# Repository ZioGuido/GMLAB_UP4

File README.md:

# GMLAB_UP4
Open-source Programmable USB Expression Pedal

This is the repository for the GMLAB UP4 pedal.

See the product at: www.GmLab.it

Buy it at www.MyRigShop.com

Visit www.GenuineSoundware.com - www.Crumar.it

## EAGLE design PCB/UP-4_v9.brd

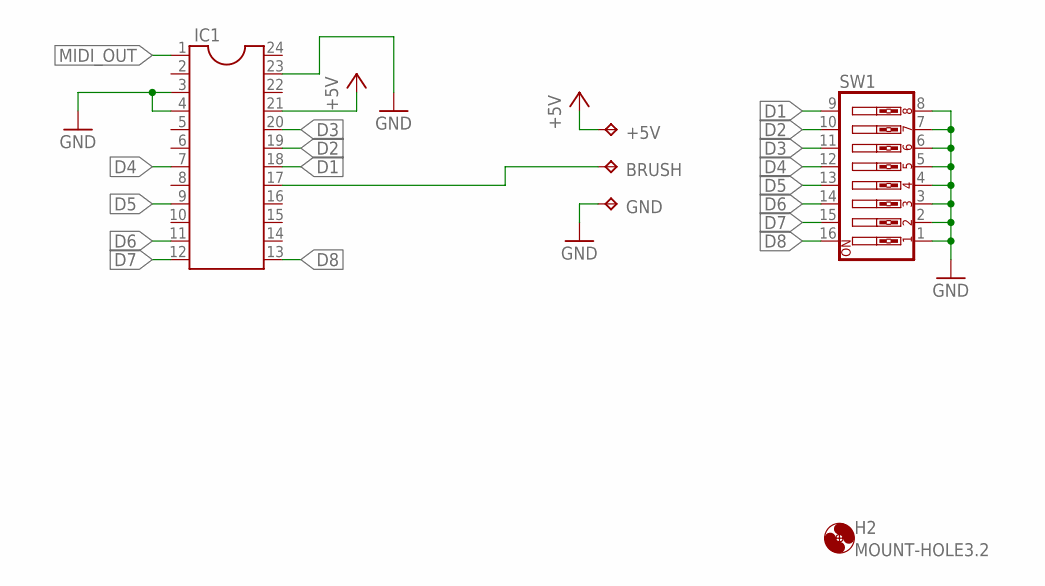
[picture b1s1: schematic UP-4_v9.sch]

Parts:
+5V: TPB2,54; B2,54
BRUSH: TPB2,54; B2,54
GND: TPB2,54; B2,54
H2: MOUNT-HOLE3.2; 3,2
IC1: DIL24-6
SW1: SW_DIP-8; EDG-08

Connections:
+5V: +5V.TP, IC1.21
BRUSH: BRUSH.TP, IC1.17
D1: IC1.18, SW1.9
D2: IC1.19, SW1.10
D3: IC1.20, SW1.11
D4: IC1.7, SW1.12
D5: IC1.9, SW1.13
D6: IC1.11, SW1.14
D7: IC1.12, SW1.15
D8: IC1.13, SW1.16
GND: GND.TP, IC1.3, IC1.4, IC1.23, SW1.1, SW1.2, SW1.3, SW1.4, SW1.5, SW1.6, SW1.7, SW1.8
MIDI_OUT: IC1.1

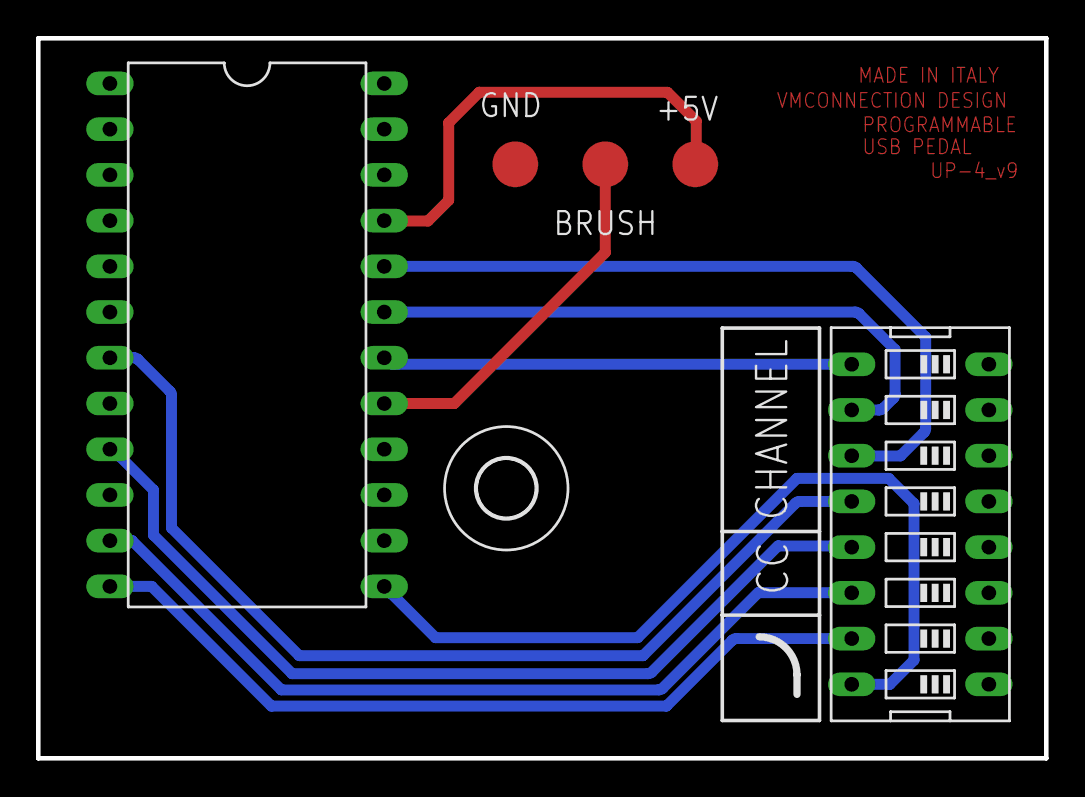
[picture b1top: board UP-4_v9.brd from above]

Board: 2 copper layers, 56.0 x 40.0 mm, 6 parts (0 on the bottom side), 11 nets.
